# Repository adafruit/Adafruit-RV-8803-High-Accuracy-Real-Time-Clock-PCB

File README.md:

## Adafruit RV-8803 High Accuracy Real Time Clock Breakout Board - STEMMA QT / Qwiic PCB

<a href="http://www.adafruit.com/products/6538"><br/>
Click here to purchase one from the Adafruit shop</a>

PCB files for the Adafruit RV-8803 High Accuracy Real Time Clock Breakout Board - STEMMA QT / Qwiic. 

Format is EagleCAD schematic and board layout
* https://www.adafruit.com/product/6538

### Description

For excellent accuracy time-keeping - when your everyday RTC (Real Time Clock) won't do - the <b>Adafruit RV-8803 Precision Real Time Clock Breakout Board</b> is a tick-tock above the rest with excellent ±1.5 ppm (at 0~50°C) accuracy. Thanks to the built-in crystal with temperature compensation management, classic RTC drift is minimized so you don't have to do any time correction with WiFi or GPS to keep current. Compare it to the popular [DS3231](https://www.adafruit.com/search?q=ds3231), with ±2 ppm (0~40°C), you get even tighter spec'd performance, at a better price!

This is a great battery-backed real time clock (RTC) that allows your microcontroller project to keep track of time even if it is reprogrammed, or if the power is lost. Perfect for data-logging, clock-building, time stamping, timers, and alarms, etc. Equipped with <b>RV-8803</b> RTC - it can run from 3.3V <i>or</i> 5V power & logic - and keep excellent time with under 50 seconds of drift over a whole year.

There's also some nifty extras like square-wave out, timer alarm, event timestamping (you can use the built in button to activate an event, or use the breakout pads)

Works great with an [Arduino using our RTC library](https://github.com/adafruit/?q=rv8803&type=all&language=&sort=), with [CircuitPython](https://github.com/adafruit/?q=rv8803&type=all&language=&sort=), or with a Raspberry Pi (or similar single board linux computer) thanks to built-in kernel support.

<b>Note: This product does not come with a CR1220 coin cell battery.</b> [We recommend you purchase a coin cell battery to use with this product](https://www.adafruit.com/product/380). The battery is required in order to keep time when power is lost, and will last at least 5 years before needing to be changed.

We've taken the RTC and put it onto a breakout PCB along with support circuitry to let you use it with 3.3V (Feather/Raspberry Pi) or 5V (Arduino/ Metro328) logic levels. Additionally, since it speaks I2C you can easily connect it up with two wires (plus power and ground!).  We've even included [SparkFun qwiic](https://www.sparkfun.com/qwiic) compatible [STEMMA QT](https://learn.adafruit.com/introducing-adafruit-stemma-qt) connectors for the I2C bus so you don't even need to solder! [QT Cable is not included](https://www.adafruit.com/?q=stemma+qt+cable&sort=BestMatch), but we have a variety in the shop. Just wire up to your favorite micro and you can use our CircuitPython/Python or [Arduino drivers](https://github.com/adafruit/RTClib) to easily interface with the RV-8803.

Comes as a fully assembled and tested breakout plus a small piece of header. You can solder header in to plug it into a breadboard, or solder wires directly.

### License

Adafruit invests time and resources providing this open source design, please support Adafruit and open-source hardware by purchasing products from [Adafruit](https://www.adafruit.com)!

Designed by Limor Fried/Ladyada for Adafruit Industries.

Creative Commons Attribution/Share-Alike, all text above must be included in any redistribution. 
See license.txt for additional details.

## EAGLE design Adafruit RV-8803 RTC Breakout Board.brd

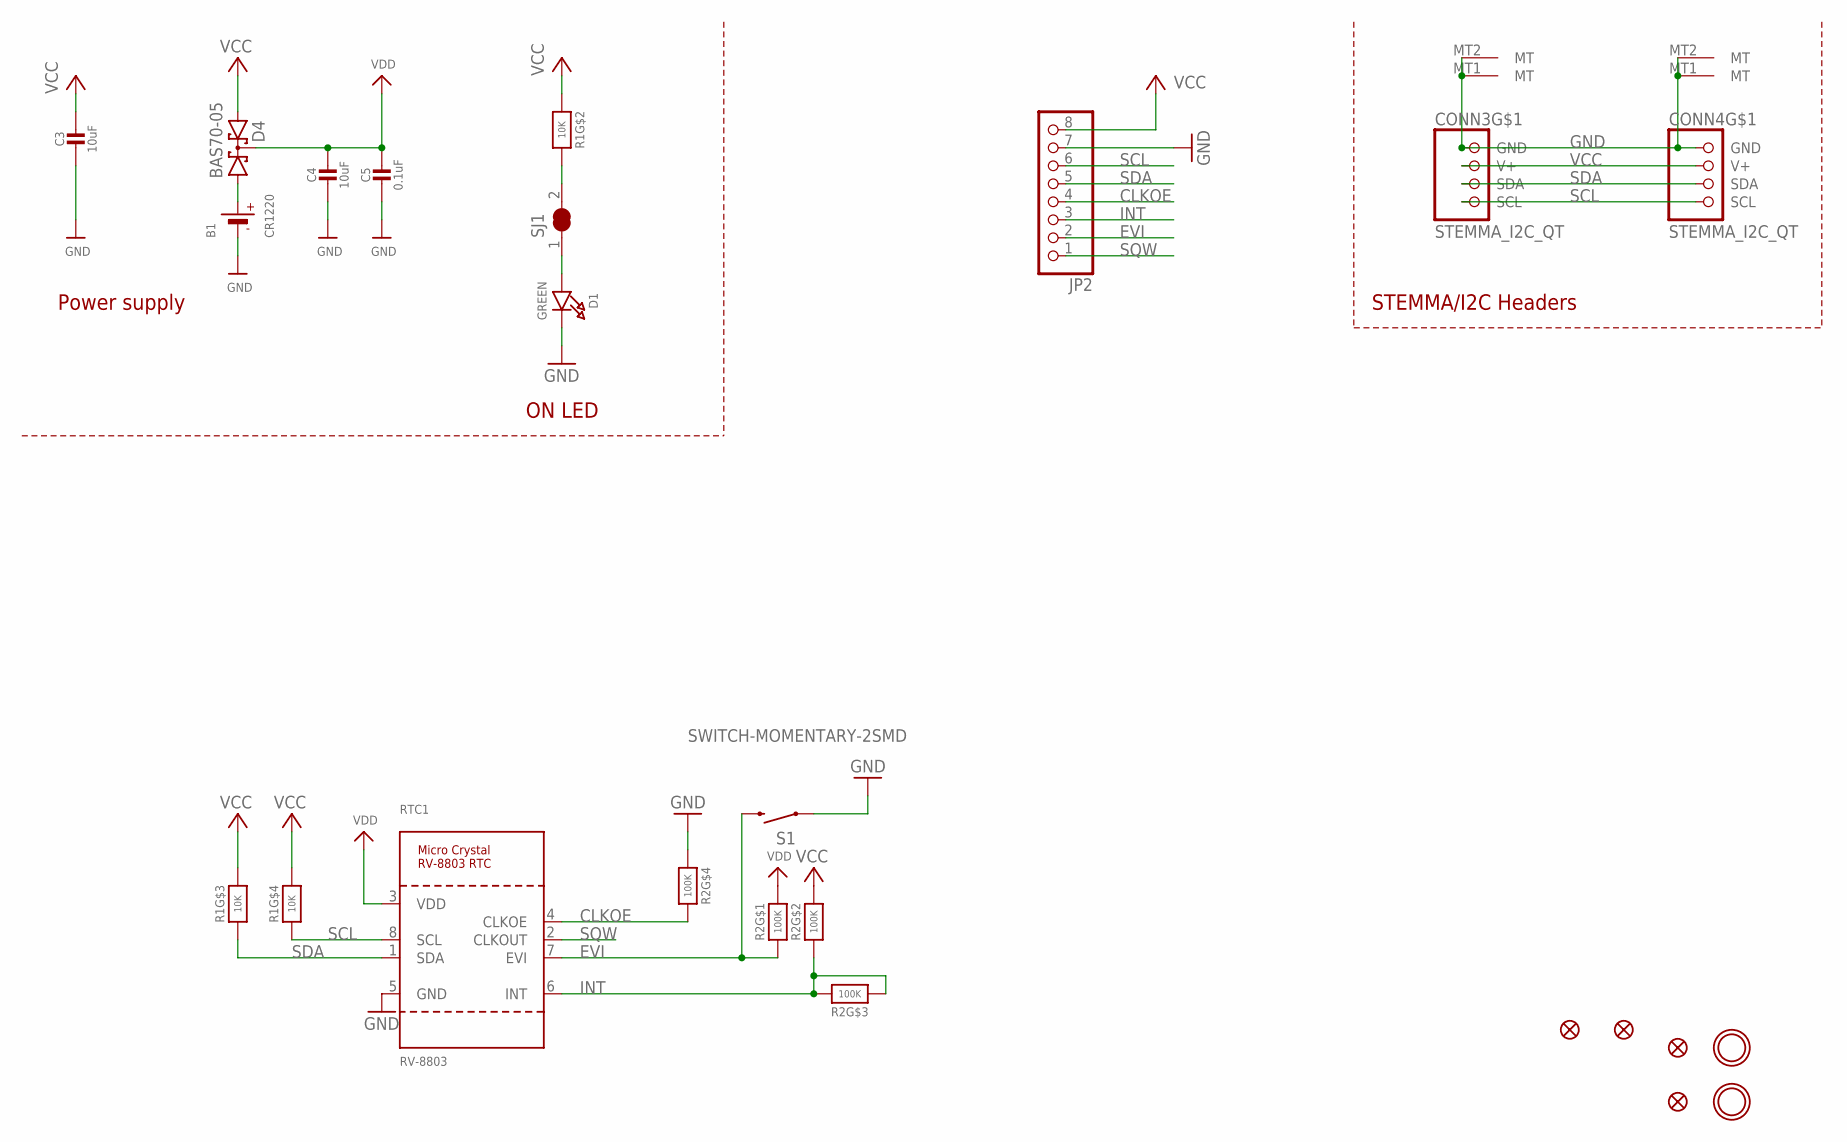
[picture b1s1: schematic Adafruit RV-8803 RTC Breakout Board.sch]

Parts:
B1: CR1220
C3, C4: 10uF; 0805-NO
C5: 0.1uF; 0603-NO
CONN3, CONN4: STEMMA_I2C_QT; JST_SH4
D1: GREEN; CHIPLED_0603_NOOUTLINE
D4: BAS70-05; SOT23
FID1, FID2, FID3, FID4: FIDUCIAL_0.5MM
JP2: HEADER-1X870MIL; 1X08_ROUND_70
R1: 10K; RESPACK_4X0603
R2: 100K; RESPACK_4X0603
RTC1: RV-8803; DFN8_RVRTC
S1: SWITCH-MOMENTARY-2SMD; TACTILE_SWITCH_SMD
SJ1: SOLDERJUMPER_CLOSED; SOLDERJUMPER_CLOSEDWIRE
U$9, U$17: MOUNTINGHOLE2.5; MOUNTINGHOLE_2.5_PLATED

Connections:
CLKOE: JP2.4, R2.5 (2), RTC1.4 (CLKOE)
EVI: JP2.2, R2.1, RTC1.7 (EVI), S1.3 (2)
GND: B1.-, C3.2, C4.2, C5.2, CONN3.1 (GND), CONN3.MT1 (MT), CONN3.MT2 (MT), CONN4.1 (GND), CONN4.MT1 (MT), CONN4.MT2 (MT), D1.C, JP2.7, R2.4 (1), RTC1.5 (GND), S1.1
INT: JP2.3, R2.2 (1), R2.3 (1), R2.6 (2), RTC1.6 (INT)
unnamed: R1.7 (2), SJ1.2
unnamed: B1.+$1 (+), B1.+$2 (+), D4.1 (A1)
unnamed: D1.A, SJ1.1
SCL: CONN3.4 (SCL), CONN4.4 (SCL), JP2.6, R1.4 (1), RTC1.8 (SCL)
SDA: CONN3.3 (SDA), CONN4.3 (SDA), JP2.5, R1.3 (1), RTC1.1 (SDA)
SQW: JP2.1, RTC1.2 (CLKOUT)
VCC: C3.1, CONN3.2 (V+), CONN4.2 (V+), D4.2 (A2), JP2.8, R1.2 (1), R1.5 (2), R1.6 (2), R2.7 (2)
VDD: C4.1, C5.1, D4.3 (CC), R2.8 (2), RTC1.3 (VDD)

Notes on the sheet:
STEMMA/I2C Headers
ON LED
Power supply

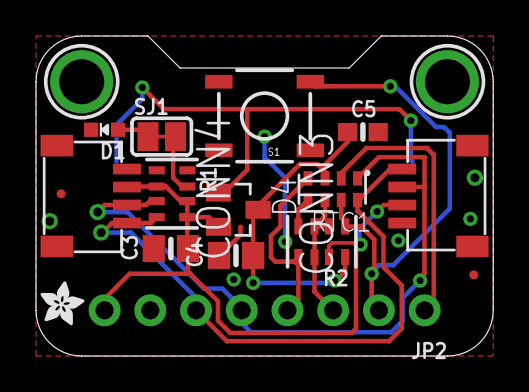
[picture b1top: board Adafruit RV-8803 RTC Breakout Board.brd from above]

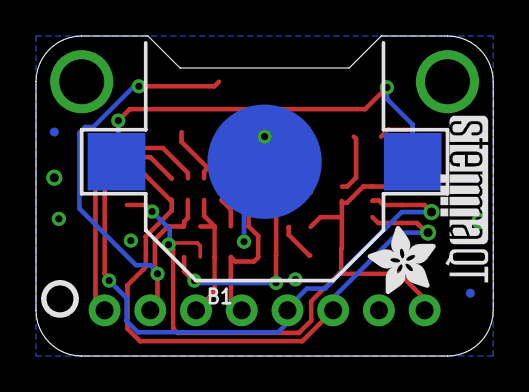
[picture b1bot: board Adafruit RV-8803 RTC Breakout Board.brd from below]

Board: 2 copper layers, 25.4 x 17.8 mm, 38 parts (8 on the bottom side), 12 nets.

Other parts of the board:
E$1: ADAFRUIT_2.5MM
PLABEL0: PLABEL0
PLABEL1: PLABEL1
PLABEL2: PLABEL2
PLABEL3: PLABEL3
PLABEL4: PLABEL4
PLABEL5: PLABEL5
PLABEL6: PLABEL6
PLABEL7: PLABEL7
PLABEL8: PLABEL8
PLABEL9: PLABEL9
PLABEL10: PLABEL10
PLABEL11: PLABEL11
PLABEL12: PLABEL12
PLABEL13: PLABEL13
U$22: ADAFRUIT_3.5MM
U$25: PCBFEAT-REV-040
U$31: STEMMAQT

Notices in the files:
parts and their libraries:
microbuilder: This work is placed in the public domain, and may be freely used for commercial and non-commercial work with the following conditions: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
SparkFun: Licensing: CC v3.0 Share-Alike You are welcome to use this library for commercial purposes.
